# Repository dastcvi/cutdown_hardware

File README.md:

# cutdown_hardware
Hardware files for the LASP high altitude balloon cutdown controller

## Versions
Different hardware revisions are tagged appropriately and can be downloaded directly from the GitHub Releases tab.

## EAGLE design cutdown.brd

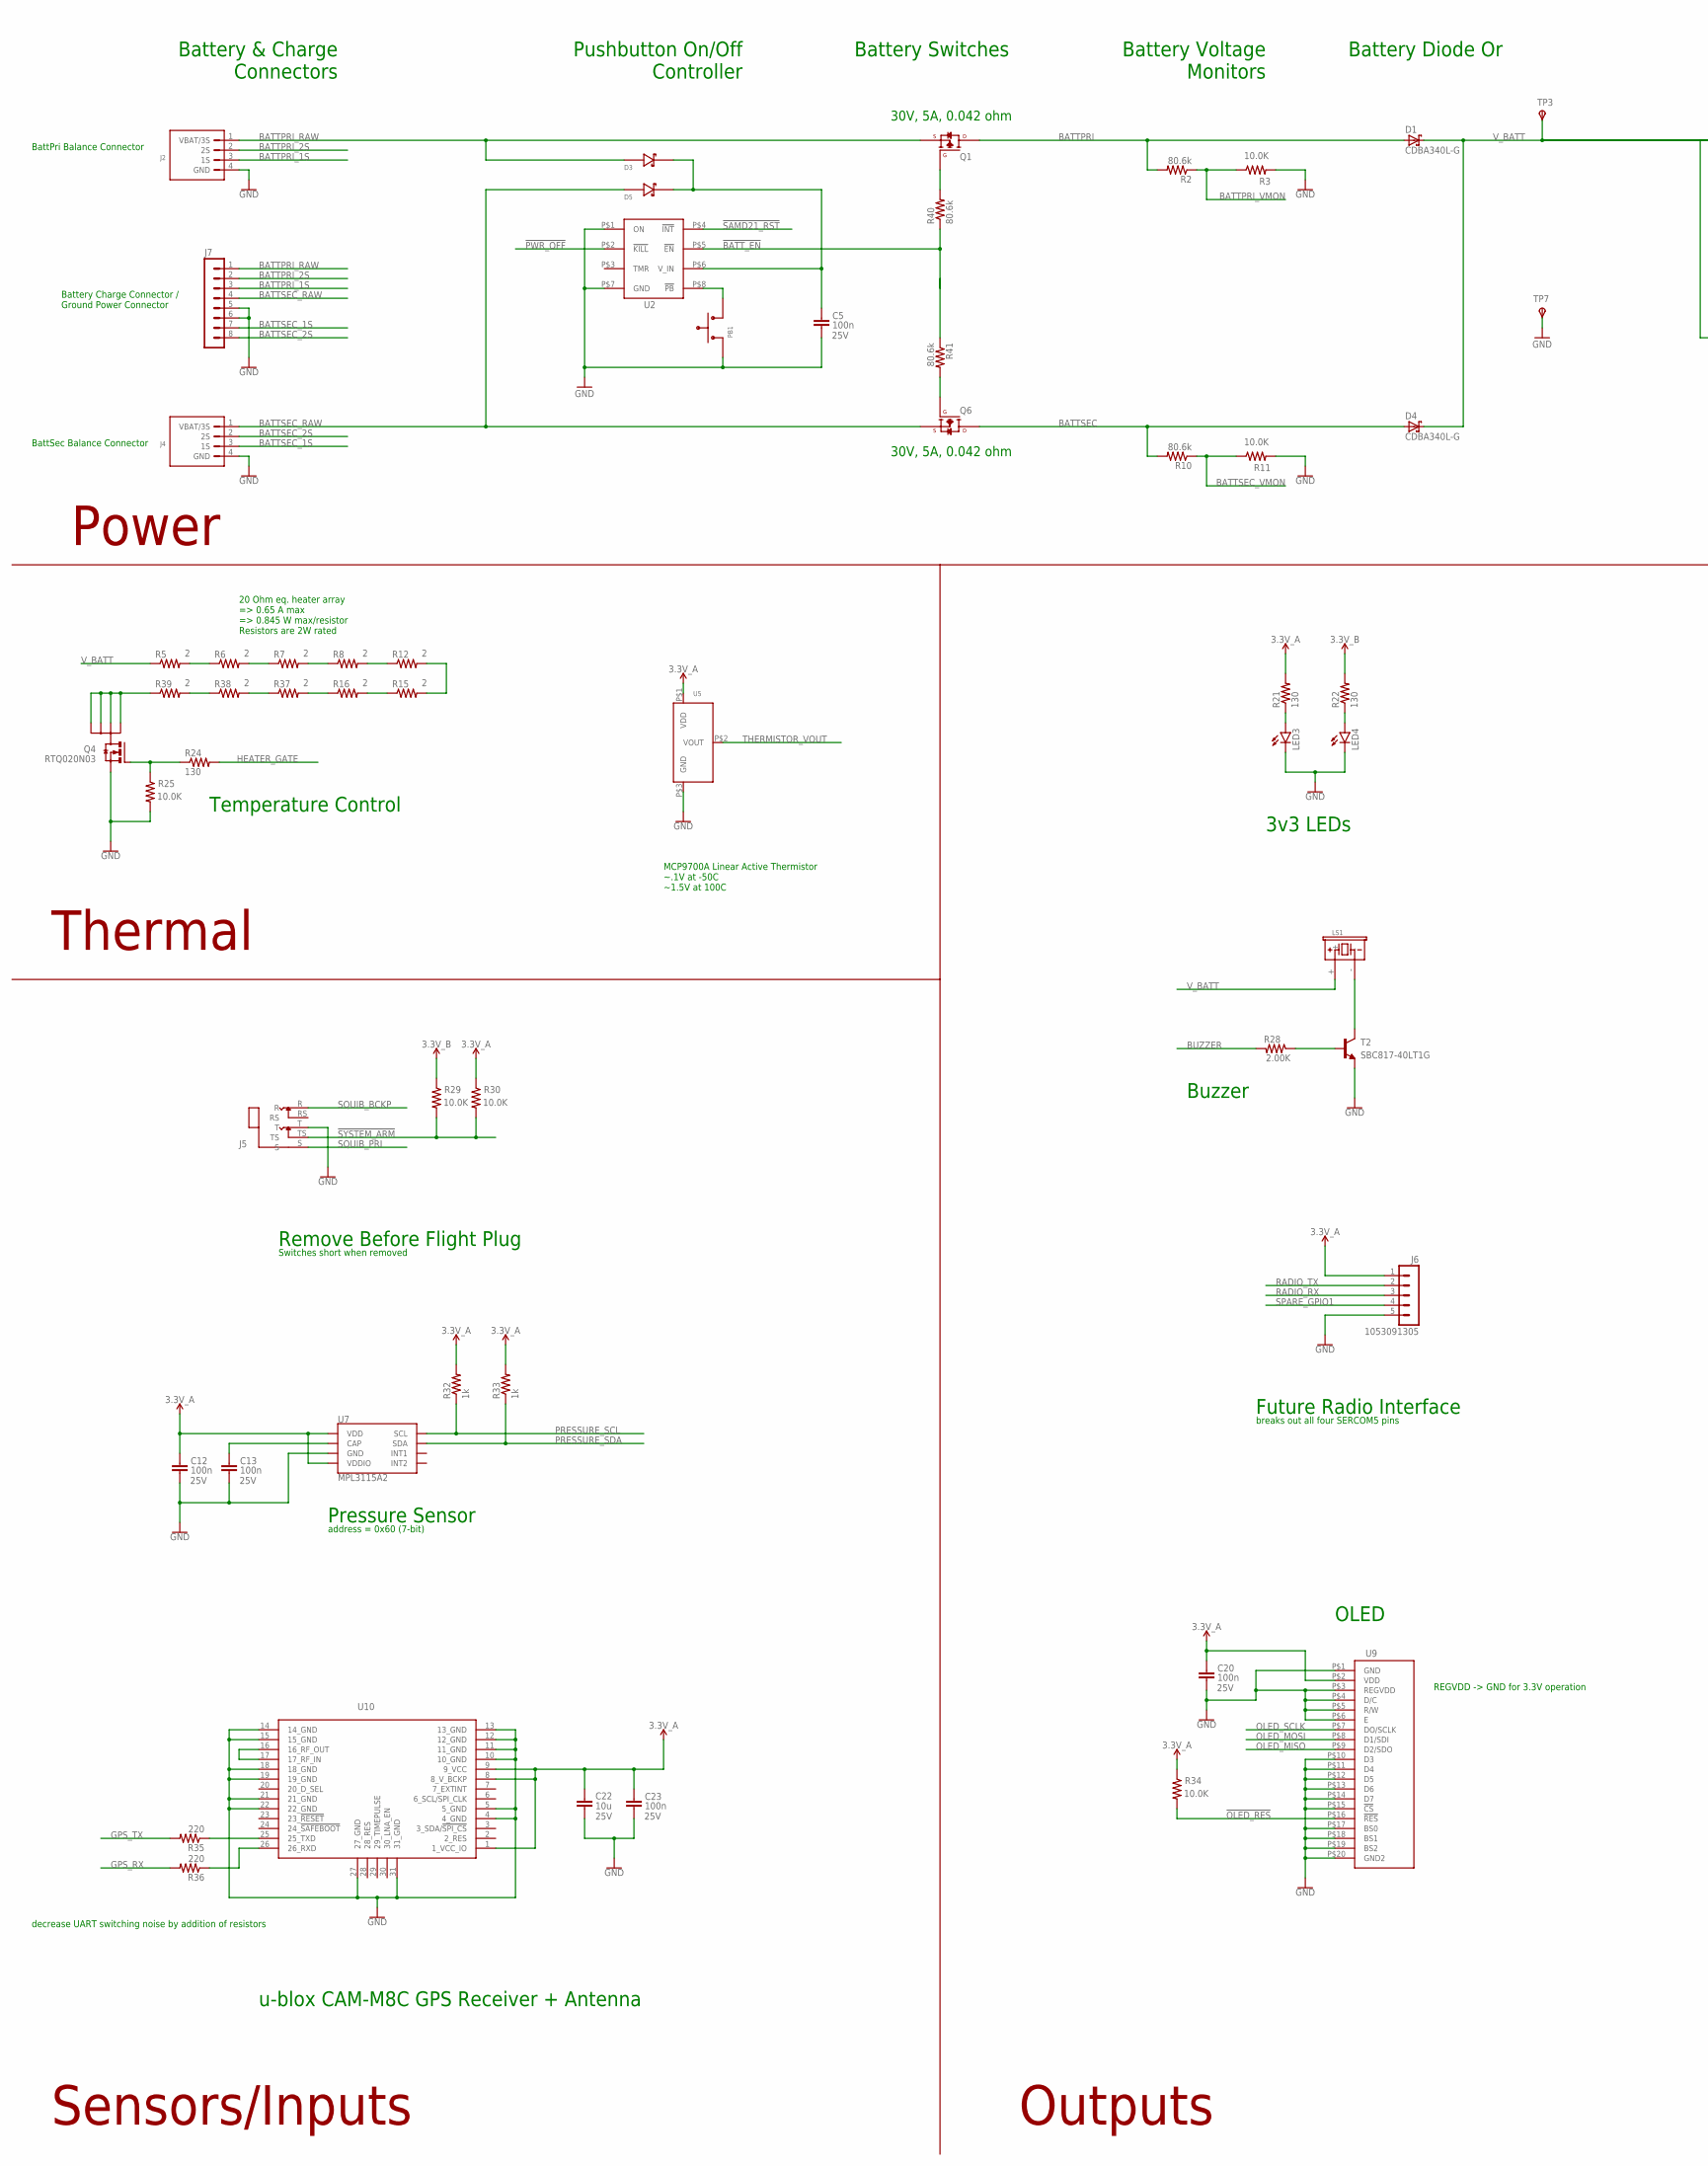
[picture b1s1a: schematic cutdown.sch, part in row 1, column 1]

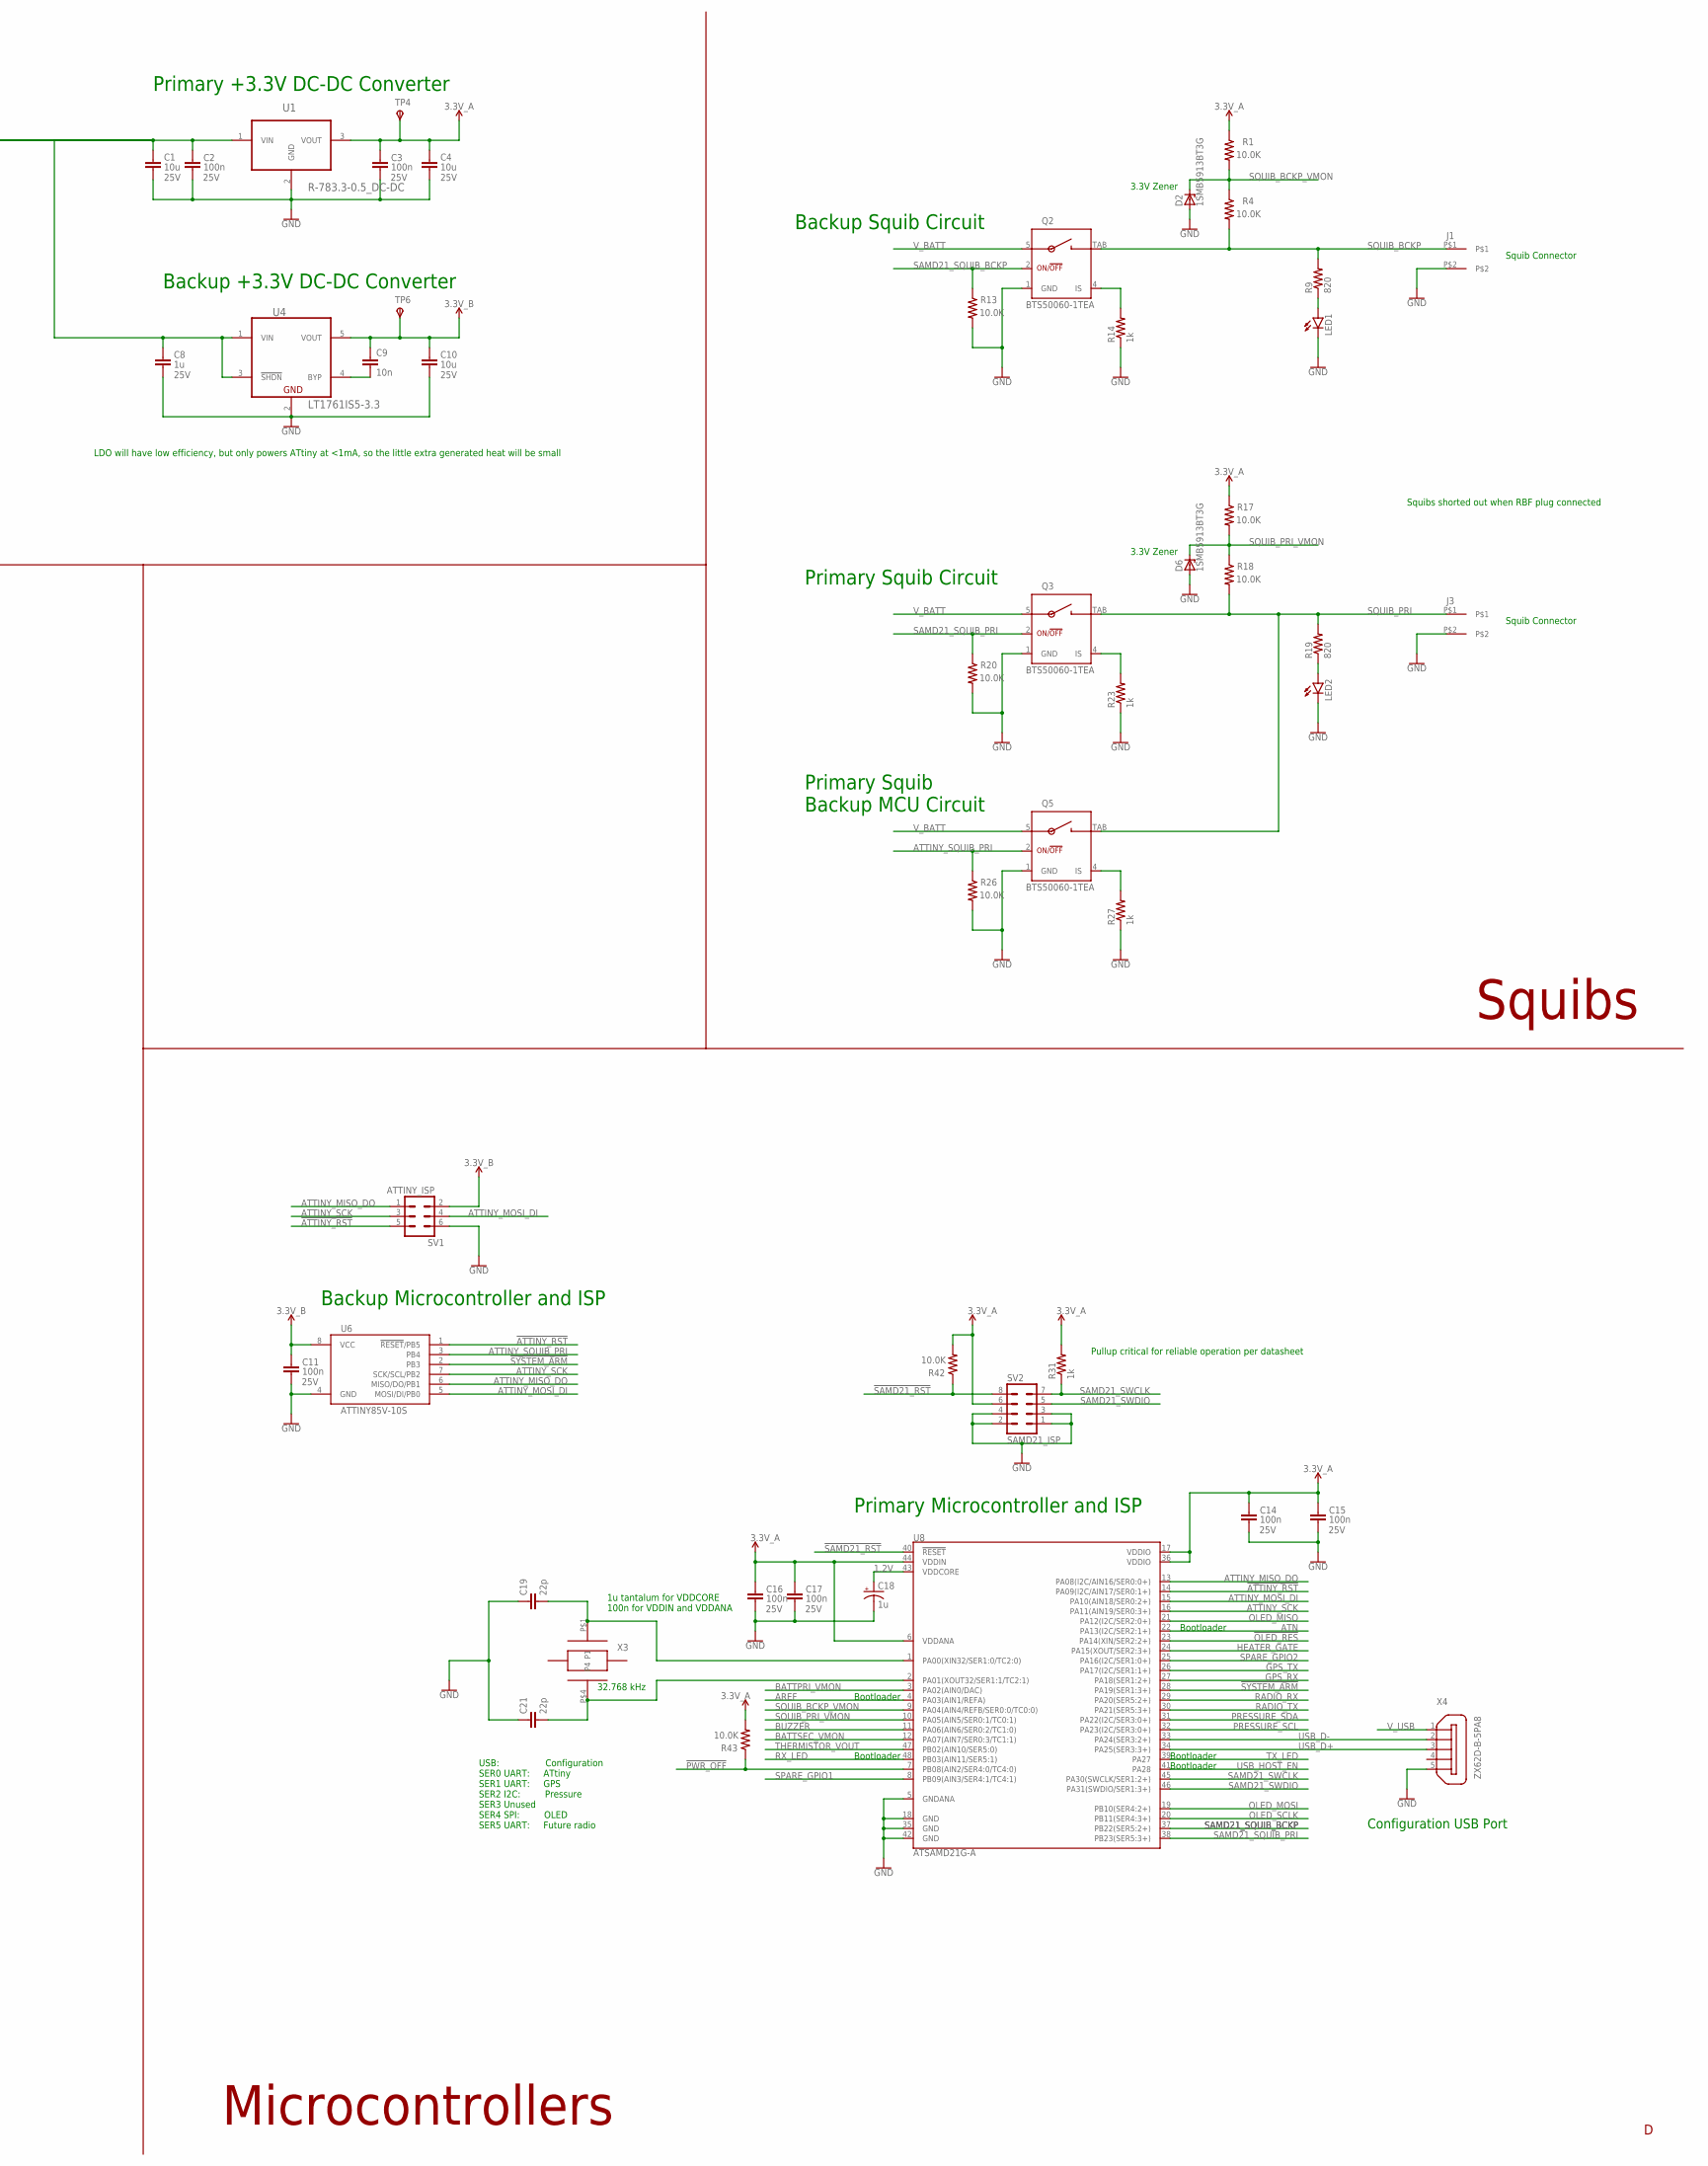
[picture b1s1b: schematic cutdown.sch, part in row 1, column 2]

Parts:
C1, C4, C10, C22: 10u; C1206; VOLTAGE 25V; MFG_PN CL31B106KAHZW6E
C2, C3, C5, C11, C12, C13, C14, C15, C16, C17, C20, C23: 100n; C0805; VOLTAGE 25V; MFG_PN 08053C104KAT2A
C8: 1u; C1206; VOLTAGE 25V; MFG_PN C1206C105K3RACTU
C9: 10n; C0805; MFG_PN C0805C103K5RACTU
C18: 1u; CT3216; MFG_PN T491A105K016AT
C19, C21: 22p; C0805; MFG_PN C0805C220K5GACTU
D1, D4: CDBA340L-G; DO214AC
D2, D6: 1SMB5913BT3G; DO214AA
D3, D5: BAT54HT1G; MFG_PN BAT54HT1G
J1, J3: DECTOR_PARTS_TR_NANOFIT_1X2_RA; DECTOR_PARTS_TR_NANOFIT_1X2_RIGHTANGLE
J2, J4: S4B-XH-SM4-TB-3S-BALANCE; S4B-XH-SM4-TB; MFG_PN S4B-XH-SM4-TB(LF)(SN)
J5: RN114BPC; MFG_PN RN114BPC
J6: 1053091305
J7: 1053141208; MFG_PN 1053141208
LED1, LED2: LEDCHIP-LED0805; CHIP-LED0805; MFG_PN LTST-C171KRKT
LED3, LED4: LEDCHIP-LED0805; CHIP-LED0805; MFG_PN LTST-C171GKT
LS1: CEM-1212C; MFG_PN CEM-1212C
PB1: FP11SPA1B1TP03; MFG_PN FP11SPA1B1TP03
Q1, Q6: SI2347DS-T1-GE3; SI1247DS; MFG_PN SI2347DS-T1-GE3
Q2, Q3, Q5: BTS50060-1TEA; PG-TO252-5-11
Q4: RTQ020N03; SC-95(TSMT6)
R1, R3, R4, R11, R13, R17, R18, R20, R25, R26, R29, R30, R34, R42, R43: 10.0K; R0805; MFG_PN ERJ-6ENF1002V
R2, R10, R40, R41: 80.6k; R0805; MFG_PN ERJ-6ENF8062V
R5, R6, R7, R8, R12, R15, R16, R37, R38, R39: 2; R2512; MFG_PN CRM2512-JW-2R0ELF
R9, R19: 820; R0805; MFG_PN ERJ-6ENF8200V
R14, R23, R27, R31, R32, R33: 1k; R0805; MFG_PN ERJ-6ENF1001V
R21, R22, R24: 130; R0805; MFG_PN ERJ-6ENF1300V
R28: 2.00K; R0805; MFG_PN ERJ-6ENF2001V
R35, R36: 220; R0805; MFG_PN ERJ-6ENF2200V
SV1: ATTINY_ISP; MA03-2; MFG_PN 67996-406HLF
SV2: SAMD21_ISP; MA04-2; MFG_PN 67996-408HLF
T2: SBC817-40LT1G; SOT23; MFG_PN SBC817-40LT1G
TP3, TP4, TP6: TPSPAD1-13; P1-13
TP7: TPSPAD1-13; P1-13; MFG_PN 5001
U1: R-783.3-0.5_DC-DC; R-783P3-0P5_DC-DC
U2: LTC2955ITS8-2; LTC2955_TSOT-8; MFG_PN LTC2955ITS8-2#TRMPBF
U4: LT1761IS5-3.3; TSOT23-5; MFG_PN LT1761IS5-3.3#TRMPBF
U5: MCP9700T-E/TT; MFG_PN MCP9700T-E/TT
U6: ATTINY85V-10S; SOIC8_EIAJ_208MIL
U7: MPL3115A2; LGA-8-5X3; MFG_PN MPL3115A2
U8: ATSAMD21G-A; TQFP-48
U9: NHD-0216CW-AW3
U10: CAM-M8C-0; CAM_M8C; MFG_PN CAM-M8C-0
X3: MC-146-32.7680KA-A0; MC-146
X4: ZX62D-B-5PA8

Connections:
1.2V: C18.+, U8.43 (VDDCORE)
!ATTINY_RST!: SV1.5, U6.1 (!RESET!/PB5), U8.14 (PA09(I2C/AIN17/SER0:1+))
!BATT_EN: R40.1, R41.1, U2.P$5 (!EN)
!OLED_RES!: R34.2, U8.23 (PA14(XIN/SER2:2+)), U9.P$16 (!RES!)
!PWR_OFF!: R43.1, U2.P$2 (!KILL), U8.7 (PB08(AIN2/SER4:0/TC4:0))
!SAMD21_RST!: R42.1, SV2.8, U2.P$4 (!INT), U8.40 (!RESET!)
!SYSTEM_ARM!: J5.TS, R29.2, R30.2, U6.2 (PB3), U8.28 (PA19(SER1:3+))
AREF: U8.4 (PA03(AIN1/REFA))
ATN: U8.22 (PA13(I2C/SER2:1+))
ATTINY_MISO_DO: SV1.1, U6.6 (MISO/DO/PB1), U8.13 (PA08(I2C/AIN16/SER0:0+))
ATTINY_MOSI_DI: SV1.4, U6.5 (MOSI/DI/PB0), U8.15 (PA10(AIN18/SER0:2+))
ATTINY_SCK: SV1.3, U6.7 (SCK/SCL/PB2), U8.16 (PA11(AIN19/SER0:3+))
ATTINY_SQUIB_PRI: Q5.2 (IN), R26.1, U6.3 (PB4)
BATTPRI: D1.A, Q1.D, R2.2
BATTPRI_1S: J2.3 (1S), J7.3
BATTPRI_2S: J2.2 (2S), J7.2
BATTPRI_RAW: D3.A, J2.1 (VBAT/3S), J7.1, Q1.S
BATTPRI_VMON: R2.1, R3.1, U8.3 (PA02(AIN0/DAC))
BATTSEC: D4.A, Q6.D, R10.2
BATTSEC_1S: J4.3 (1S), J7.7
BATTSEC_2S: J4.2 (2S), J7.8
BATTSEC_RAW: D5.A, J4.1 (VBAT/3S), J7.4, Q6.S
BATTSEC_VMON: R10.1, R11.1, U8.12 (PA07(AIN7/SER0:3/TC1:1))
BUZZER: R28.2, U8.11 (PA06(AIN6/SER0:2/TC1:0))
GND: C1.2, C2.2, C3.2, C4.2, C5.2, C8.2, C10.2, C11.2, C12.2, C13.2, C14.2, C15.2, C16.2, C17.2, C18.-, C19.1, C20.2, C21.1, C22.2, C23.2, D2.A, D6.A, J1.P$2, J2.4 (GND), J3.P$2, J4.4 (GND), J5.T, J6.5, J7.5, J7.6, LED1.C, LED2.C, LED3.C, LED4.C, PB1.1, Q2.1 (GND), Q3.1 (GND), Q4.4 (S), Q5.1 (GND), R3.2, R11.2, R13.2, R14.1, R20.2, R23.1, R25.2, R26.2, R27.1, SV1.6, SV2.1, SV2.2, SV2.3, SV2.4, T2.2 (E), TP7.TP, U1.2 (GND), U2.P$1 (ON), U2.P$7 (GND), U4.2 (GND), U5.P$3 (GND), U6.4 (GND), U7.3 (GND), U8.5 (GNDANA), U8.18 (GND), U8.35 (GND), U8.42 (GND), U9.P$1 (GND), U9.P$3 (REGVDD), U9.P$4 (D/C), U9.P$5 (R/W), U9.P$6 (E), U9.P$10 (D3), U9.P$11 (D4), U9.P$12 (D5), U9.P$13 (D6), U9.P$14 (D7), U9.P$15 (!CS!), U9.P$17 (BS0), U9.P$18 (BS1), U9.P$19 (BS2), U9.P$20 (GND2), U10.4 (4_GND), U10.5 (5_GND), U10.10 (10_GND), U10.11 (11_GND), U10.12 (12_GND), U10.13 (13_GND), U10.14 (14_GND), U10.15 (15_GND), U10.18 (18_GND), U10.19 (19_GND), U10.21 (21_GND), U10.22 (22_GND), U10.27 (27_GND), U10.31 (31_GND), X4.5
GPS_RX: R36.2, U8.27 (PA18(SER1:2+))
GPS_TX: R35.2, U8.26 (PA17(I2C/SER1:1+))
HEATER_GATE: R24.2, U8.24 (PA15(XOUT/SER2:3+))
unnamed: R28.1, T2.1 (B)
unnamed: R5.2, R6.1
unnamed: Q1.G, R40.2
unnamed: R6.2, R7.1
unnamed: R7.2, R8.1
unnamed: R8.2, R12.1
unnamed: R12.2, R15.2
unnamed: C13.1, U7.2 (CAP)
unnamed: U10.16 (16_RF_OUT), U10.17 (17_RF_IN)
unnamed: R35.1, U10.25 (25_TXD)
unnamed: C21.2, U8.2 (PA01(XOUT32/SER1:1/TC2:1)), X3.P$4 (P4)
unnamed: LED3.A, R21.1
unnamed: Q2.4 (IS), R14.2
unnamed: LED4.A, R22.1
unnamed: LED1.A, R9.1
unnamed: R15.1, R16.2
unnamed: R16.1, R37.2
unnamed: Q3.4 (IS), R23.2
unnamed: Q5.4 (IS), R27.2
unnamed: LED2.A, R19.1
unnamed: R37.1, R38.2
unnamed: Q4.3 (G), R24.1, R25.1
unnamed: C19.2, U8.1 (PA00(XIN32/SER1:0/TC2:0)), X3.P$1 (P1)
unnamed: R38.1, R39.2
unnamed: LS1.-, T2.3 (C)
unnamed: C9.2, U4.4 (BYP)
unnamed: R36.1, U10.26 (26_RXD)
unnamed: Q4.1 (D), Q4.2 (D), Q4.5 (D), Q4.6 (D6), R39.1
unnamed: Q6.G, R41.2
unnamed: PB1.3, U2.P$8 (!PB)
unnamed: C5.1, D3.C, D5.C, U2.P$6 (V_IN)
OLED_MISO: U8.21 (PA12(I2C/SER2:0+)), U9.P$9 (D2/SDO)
OLED_MOSI: U8.19 (PB10(SER4:2+)), U9.P$8 (D1/SDI)
OLED_SCLK: U8.20 (PB11(SER4:3+)), U9.P$7 (DO/SCLK)
PRESSURE_SCL: R32.1, U7.8 (SCL), U8.32 (PA23(I2C/SER3:0+))
PRESSURE_SDA: R33.1, U7.7 (SDA), U8.31 (PA22(I2C/SER3:0+))
RADIO_RX: J6.3, U8.29 (PA20(SER5:2+))
RADIO_TX: J6.2, U8.30 (PA21(SER5:3+))
RX_LED: U8.48 (PB03(AIN11/SER5:1))
SAMD21_SQUIB_BCKP: Q2.2 (IN), R13.1, U8.37 (PB22(SER5:2+))
SAMD21_SQUIB_PRI: Q3.2 (IN), R20.1, U8.38 (PB23(SER5:3+))
SAMD21_SWCLK: R31.1, SV2.7, U8.45 (PA30(SWCLK/SER1:2+))
SAMD21_SWDIO: SV2.5, U8.46 (PA31(SWDIO/SER1:3+))
SPARE_GPIO1: J6.4, U8.8 (PB09(AIN3/SER4:1/TC4:1))
SPARE_GPIO2: U8.25 (PA16(I2C/SER1:0+))
SQUIB_BCKP: J1.P$1, J5.R, Q2.TAB (OUT), R4.2, R9.2
SQUIB_BCKP_VMON: D2.C, R1.2, R4.1, U8.9 (PA04(AIN4/REFB/SER0:0/TC0:0))
SQUIB_PRI: J3.P$1, J5.S, Q3.TAB (OUT), Q5.TAB (OUT), R18.2, R19.2
SQUIB_PRI_VMON: D6.C, R17.2, R18.1, U8.10 (PA05(AIN5/SER0:1/TC0:1))
THERMISTOR_VOUT: U5.P$2 (VOUT), U8.47 (PB02(AIN10/SER5:0))
TX_LED: U8.39 (PA27)
USB_D+: U8.34 (PA25(SER3:3+)), X4.3
USB_D-: U8.33 (PA24(SER3:2+)), X4.2
USB_HOST_EN: U8.41 (PA28)
VCC_1: C3.1, C4.1, C12.1, C14.1, C15.1, C16.1, C17.1, C20.1, C22.1, C23.1, J6.1, R1.1, R17.1, R21.2, R30.1, R31.2, R32.2, R33.2, R34.1, R42.2, R43.2, SV2.6, TP4.TP, U1.3 (VOUT), U5.P$1 (VDD), U7.1 (VDD), U7.4 (VDDIO), U8.6 (VDDANA), U8.17 (VDDIO), U8.36 (VDDIO), U8.44 (VDDIN), U9.P$2 (VDD), U10.1 (1_VCC_IO), U10.8 (8_V_BCKP), U10.9 (9_VCC)
VCC_2: C9.1, C10.1, C11.1, R22.2, R29.1, SV1.2, TP6.TP, U4.5 (VOUT), U6.8 (VCC)
V_BATT: C1.1, C2.1, C8.1, D1.C, D4.C, LS1.+, Q2.5 (VS), Q3.5 (VS), Q5.5 (VS), R5.1, TP3.TP, U1.1 (VIN), U4.1 (VIN), U4.3 (!SHDN)
V_USB: X4.1

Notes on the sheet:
Backup Microcontroller and ISP
Primary Microcontroller and ISP
1u tantalum for VDDCORE 100n for VDDIN and VDDANA
BattPri Balance Connector
Primary +3.3V DC-DC Converter
Backup +3.3V DC-DC Converter
Pullup critical for reliable operation per datasheet
Configuration USB Port
u-blox CAM-M8C GPS Receiver + Antenna
Pressure Sensor
USB: Configuration SER0 UART: ATtiny SER1 UART: GPS SER2 I2C: Pressure SER3 Unused SER4 SPI: OLED SER5 UART: Future radio
BattSec Balance Connector
Battery & Charge Connectors
address = 0x60 (7-bit)
OLED
Remove Before Flight Plug
Switches short when removed
3.3V Zener
Backup Squib Circuit
Primary Squib Circuit
Primary Squib Backup MCU Circuit
Temperature Control
Future Radio Interface
breaks out all four SERCOM5 pins
32.768 kHz
30V, 5A, 0.042 ohm
3v3 LEDs
Squib Connector
Buzzer
MCP9700A Linear Active Thermistor ~.1V at -50C ~1.5V at 100C
Power
Squibs
Microcontrollers
Outputs
Sensors/Inputs
Thermal
Squibs shorted out when RBF plug connected
REGVDD -> GND for 3.3V operation
Bootloader
LDO will have low efficiency, but only powers ATtiny at <1mA, so the little extra generated heat will be small

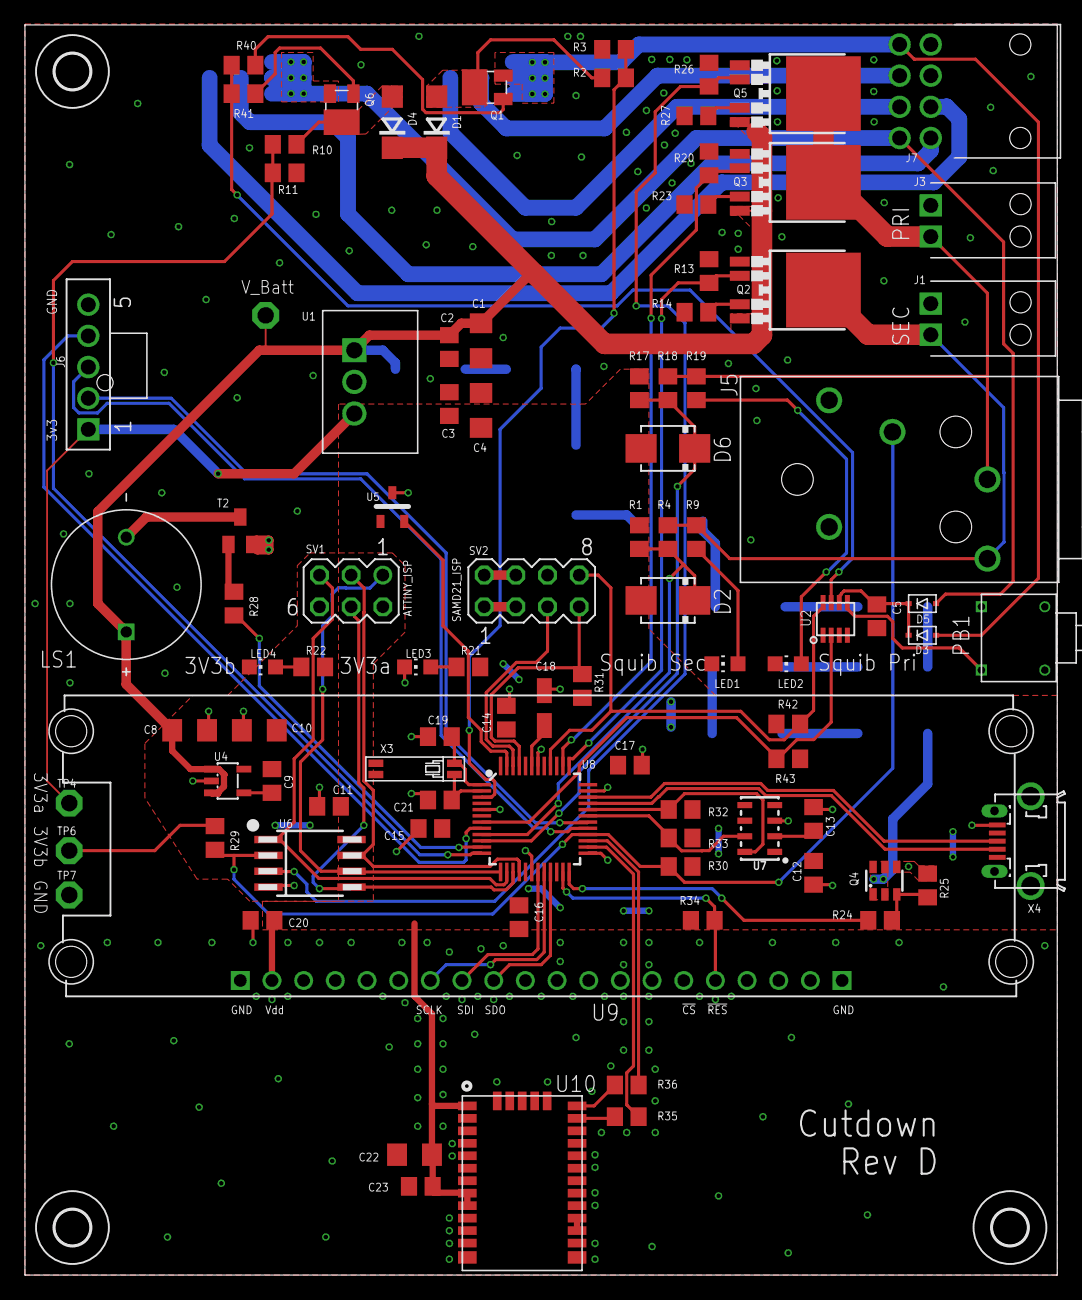
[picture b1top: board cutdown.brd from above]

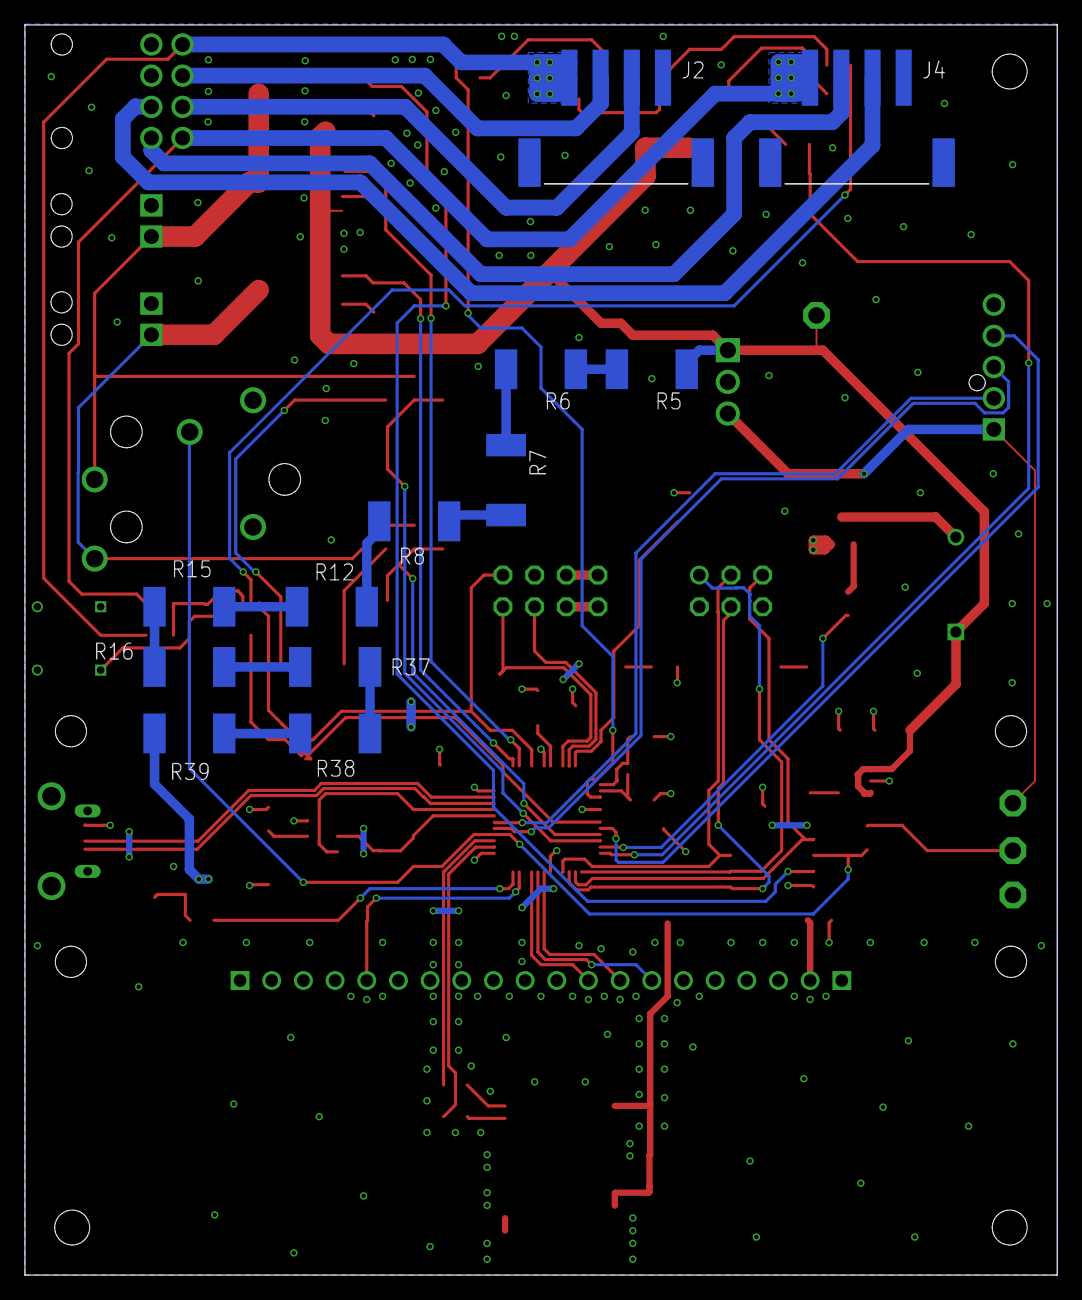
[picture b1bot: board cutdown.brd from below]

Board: 2 copper layers, 82.8 x 100.3 mm, 110 parts (12 on the bottom side), 79 nets.

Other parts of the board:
U$16, U$17, U$18: 2,8

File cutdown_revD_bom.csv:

Item Number,Reference Designator,Manufacturer,Description,Manufacturer Part Number,Qty,Instructions
1,"LED3, LED4",Lite-On,LED GREEN CLEAR CHIP SMD,LTST-C171GKT,2,
2,"LED1, LED2",Lite-On,LED RED CLEAR SMD,LTST-C171KRKT,2,
3,"R1, R3, R4, R11, R13, R17, R18, R20, R25, R26, R29, R30, R34, R42, R43",Panasonic,RES SMD 10.0K OHM 1% 1/8W 0805,ERJ-6ENF1002V,15,
4,"C2, C3, C5, C11, C12, C13, C14, C15, C16, C17, C20, C23",AVX,CAP CER 0.1UF 25V X7R 0805,08053C104KAT2A,12,
5,J6,Molex,CONN HEADER VERT 5POS 2.5MM,1053091305,1,
6,J7,Molex,CONN HEADER R/A 8POS 2.5MM,1053141208,1,
7,C9,Kemet,CAP CER 10000PF 50V X7R 0805,C0805C103K5RACTU,1,
8,"C1, C4, C10, C22",Samsung,CAP CER 10UF 25V X7R 1206,CL31B106KAHZW6E,4,
9,"R21, R22, R24",Panasonic,RES SMD 130 OHM 1% 1/8W 0805,ERJ-6ENF1300V,3,
10,"D2, D6",ON Semiconductor,DIODE ZENER 3.3V 3W SMB,1SMB5913BT3G,2,
11,"R14, R23, R27, R31, R32, R33",Panasonic,RES SMD 1K OHM 1% 1/8W 0805,ERJ-6ENF1001V,6,
12,C8,Kemet,CAP CER 1UF 25V X7R 1206,C1206C105K3RACTU,1,
13,C18,Kemet,CAP TANT 1UF 10% 16V 1206,T491A105K016AT,1,
14,"R5, R6, R7, R8, R12, R15, R16, R37, R38, R39",Bourns Inc.,RES SMD 2 OHM 5% 2W 2512,CRM2512-JW-2R0ELF,10,"Purchase, DNI"
15,R28,Panasonic,RES SMD 2.00K OHM 1% 1/8W 0805,ERJ-6ENF2001V,1,
16,"R35, R36",Panasonic,RES SMD 220 OHM 1% 1/8W 0805,ERJ-6ENF2200V,2,
17,"C19, C21",Kemet,CAP CER 22PF 50V C0G/NP0 0805,C0805C220K5GACTU,2,
18,"R2, R10, R40, R41",Panasonic,RES SMD 80.6K OHM 1% 1/8W 0805,ERJ-6ENF8062V,4,
19,"R9, R19",Panasonic,RES SMD 820 OHM 1% 1/8W 0805,ERJ-6ENF8200V,2,
20,U8,Atmel,IC MCU 32BIT 256KB FLASH 48TQFP,ATSAMD21G18A-AUT,1,
21,U6,Atmel,IC MCU 8BIT 8KB FLASH 8SOIC,ATTINY85V-10SU,1,
22,SV1,Amphenol,CONN HEADER 6POS .100 STR TIN,67996-406HLF,1,
23,"D3, D5",ON Semiconductor,DIODE SCHOTTKY 30V 200MA SOD323,BAT54HT1G,2,
24,"Q2, Q3, Q5",Infineon,PWR SW HI-SIDE 1CH TO252-5,   BTS500601TEAAUMA2,3,
25,U10,U-Blox America Inc.,RF RCVR GNSS/GPS 1.575GHZ MODULE,CAM-M8C-0,1,
26,"D1, D4",COMCHIP,DIODE SCHOTTKY 40V 3A DO214AC,CDBA340L-G,2,
27,LS1,CUI Devices,AUDIO MAGNETIC IND 8-16V TH,CEM-1212C,1,
28,"J1, J3",Molex,CONN HEADER R/A 2POS 2.5MM,1053131102,2,
29,PB1,C&G,SWITCH PUSH SPST-NO 0.4VA 28V,FP11SPA1B1TP03,1,
30,U4,Linear Technology,IC REG LIN 3.3V 100MA TSOT23-5,LT1761IS5-3.3#TRMPBF,1,
31,U2,Linear Technology/Analog Devices,IC CTLR ON/OFF PUSHBUTT TSOT23-8,LTC2955ITS8-2#TRMPBF,1,
32,X3,Epson,CRYSTAL 32.7680 KHZ 12.5PF SMD,MC-146 32.7680KA-A0:ROHS,1,
33,U5,Microchip Technology,SENSOR ANALOG -40C-125C SOT23-3,MCP9700T-E/TT,1,
34,U7,NXP,IC ALTIMETER I2C VERSION 8LGA,MPL3115A2,1,
35,U9,Newhaven,2X16 WHITE SLIM CHARACTER OLED,NHD-0216CW-AW3,1,"Purchase, DNI"
36,U1,RECOM,DC DC CONVERTER 3.3V 3W,R-783.3-0.5,1,
37,J5,Switchcraft Inc.,CONN JACK STEREO 6.35MM R/A,RN114BPC,1,
38,Q4,Rohm,MOSFET N-CH 30V 2A TSMT6,RTQ020N03TR,1,
39,"J2, J4",JST Sales America Inc.,CONN HEADER SMD R/A 4POS 2.5MM,S4B-XH-SM4-TB(LF)(SN),2,"Purchase, DNI"
40,SV2,Amphenol,CONN HEADER 8POS .100 STR TIN,67996-408HLF,1,
41,T2,On Semi,TRANS NPN 45V 0.5A SOT-23,SBC817-40LT1G,1,
42,"Q1, Q6",Vishay Siliconix,MOSFET P-CH 30V 5A SOT-23,SI2347DS-T1-GE3,2,
43,X4,Hirose,CONN RCPT USB MICRO B 2.0 5P SMD,ZX62D-B-5PA8(30),1,

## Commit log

2018-12-04 Added Rev A files
2019-01-24 Rev B Hardware
2019-01-24 Created README
2020-07-08 Rev D files

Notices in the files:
parts and their libraries:
SparkFun-Sensors: Licensing: Creative Commons ShareAlike 4.0 International - https://creativecommons.org/licenses/by-sa/4.0
